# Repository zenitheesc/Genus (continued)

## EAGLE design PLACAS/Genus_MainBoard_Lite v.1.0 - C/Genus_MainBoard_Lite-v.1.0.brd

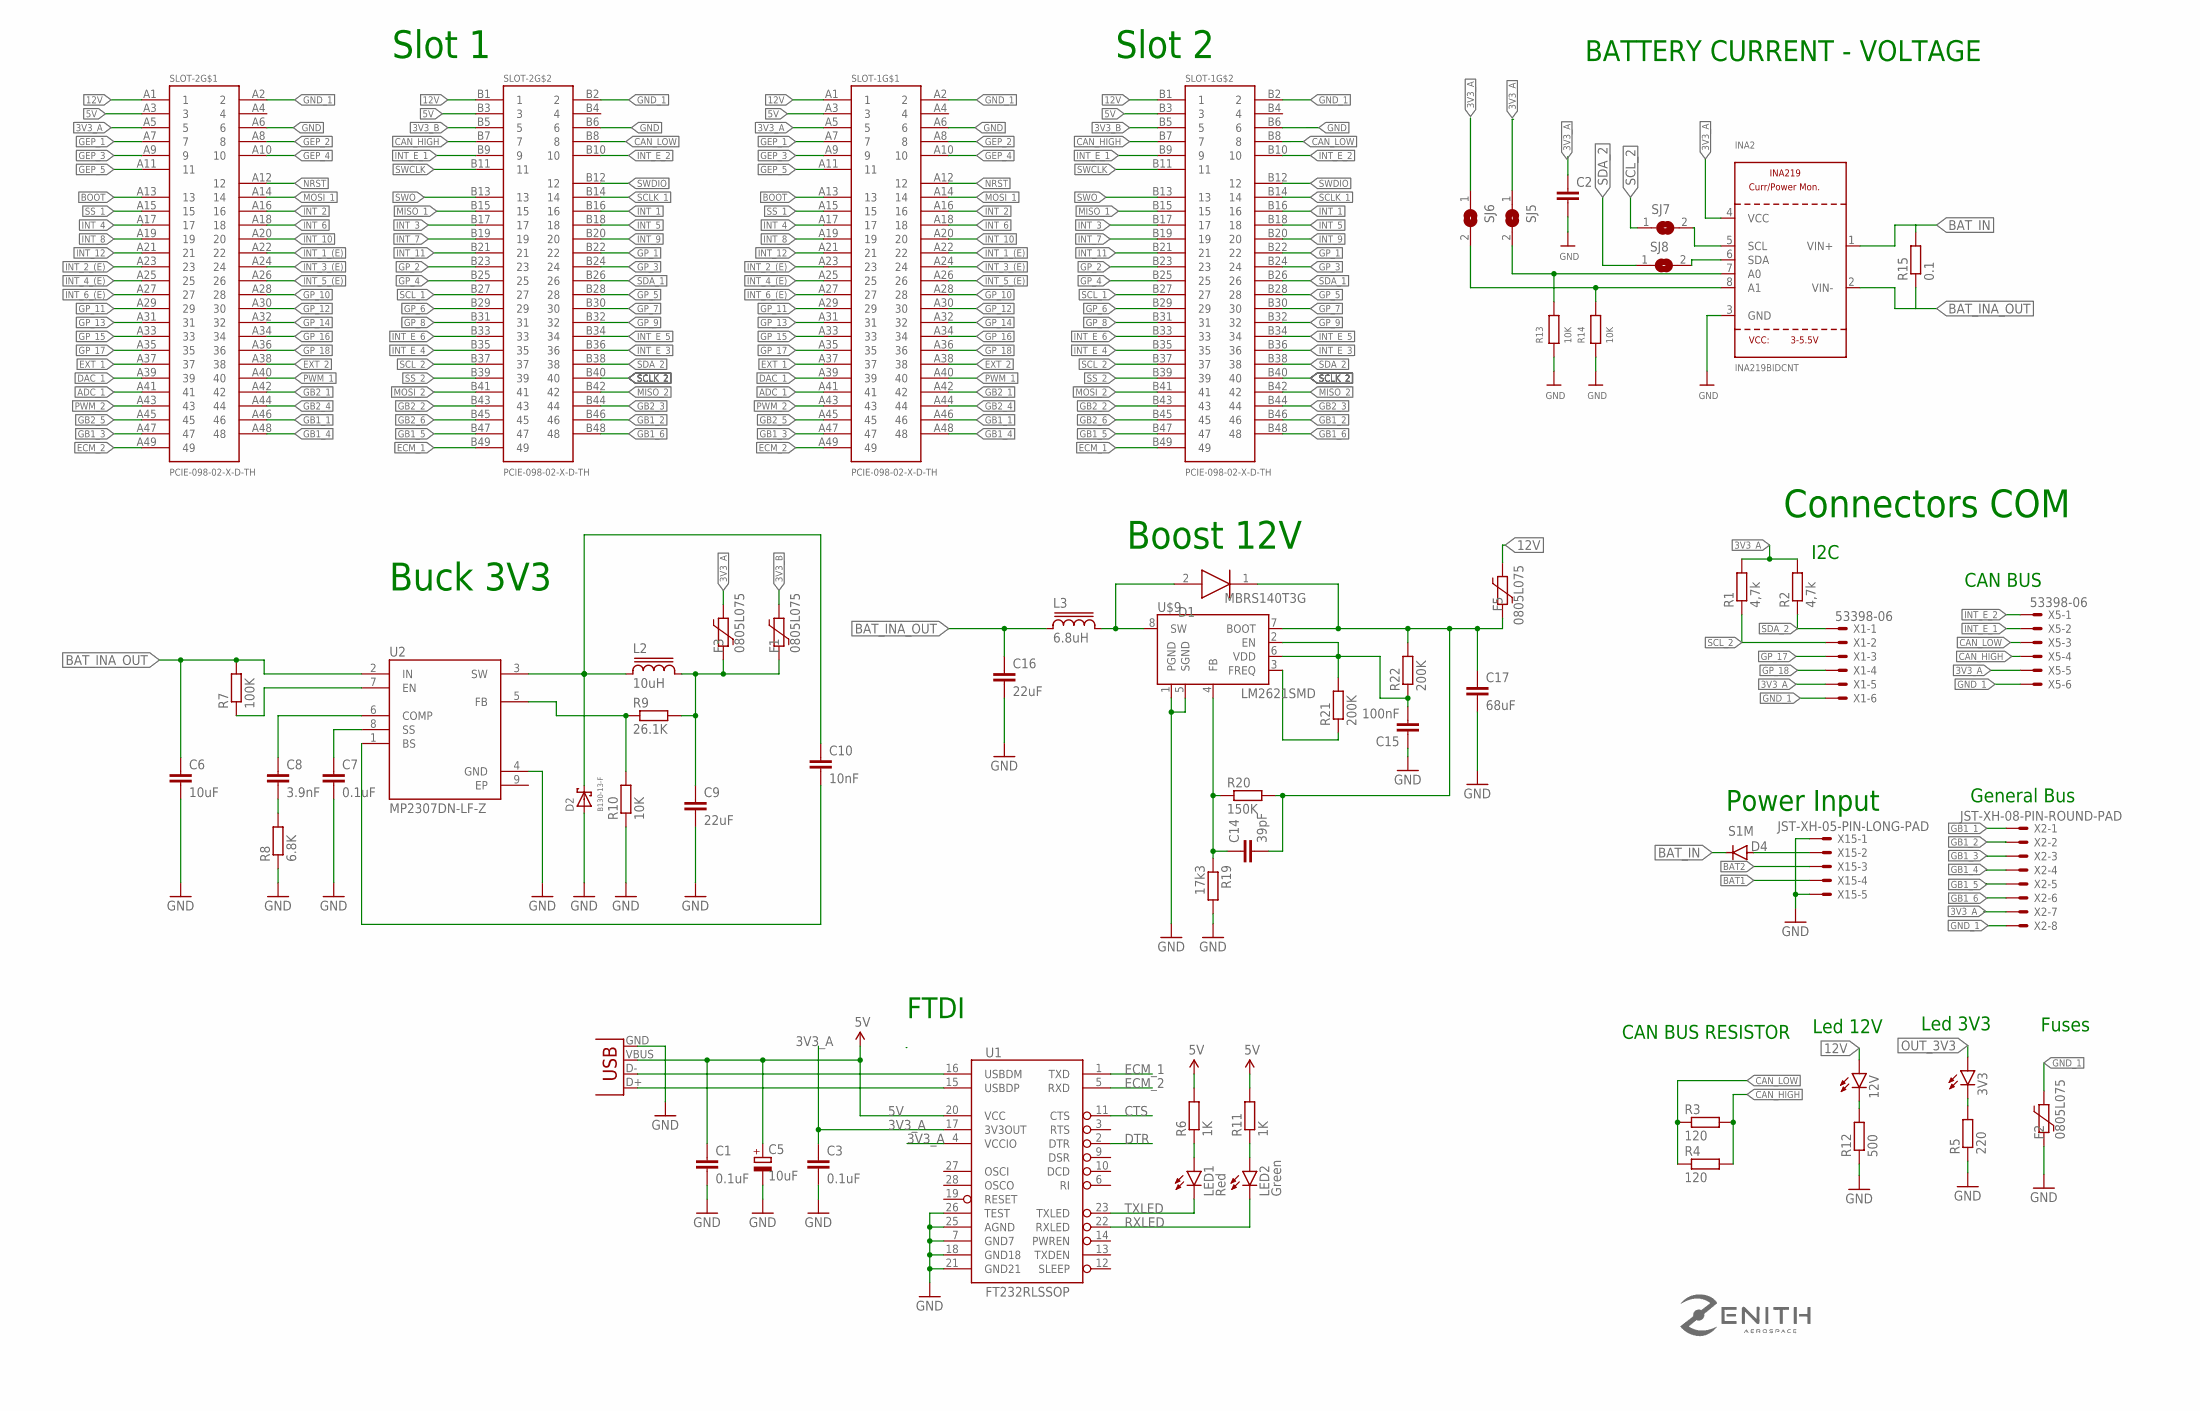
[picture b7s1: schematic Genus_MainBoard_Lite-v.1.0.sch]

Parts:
3V3, 12V: LEDCHIP-LED0805; CHIP-LED0805
C1, C3, C7: 0.1uF; C0805
C2: C-EUC0805; C0805
C5: 10uF; PANASONIC_B
C6: 10uF; C0805
C8: 3.9nF; C0805
C9: 22uF; C0805
C10: 10nF; C0805
C14: 39pF; C0805
C15: 100nF; C0805
C16: 22uF; C1210
C17: 68uF; C1210
D1: MBRS140T3G; DIOM5436X247N
D2: B130-13-F; SMA
D4: S1M; SMA
F1, F2, F3, F5: 0805L075; 0805L
INA2: INA219BIDCNT; SOT23-8
L2: 10uH; SRR1280
L3: 6.8uH; SRR1280
LED1: Red; CHIPLED_0805
LED2: Green; CHIPLED_0805
R1, R2: 4,7k; R0805
R3, R4: 120; R0805
R5: 220; R0805
R6, R11: 1K; R0805
R7: 100K; R0805
R8: 6.8K; R0805
R9: 26.1K; R0805
R10, R13, R14: 10K; R0805
R12: 500; R0805
R15: 0.1; R2512
R19: 17k3; R0805
R20: 150K; R0805
R21, R22: 200K; R0805
SJ5, SJ6, SJ7, SJ8: SOLDERJUMPERREFLOW_NOPASTE; SOLDERJUMPER_REFLOW_NOPASTE
SLOT-1, SLOT-2: PCIE-098-02-X-D-TH
U1: FT232RLSSOP; SSOP28DB
U2: MP2307DN-LF-Z; SOIC127P600X170-9N
U$9: LM2621SMD; MSOP-8
X1, X5: 53398-06
X2: JST-XH-08-PIN-ROUND-PAD; JST-XH-08-PACKAGE-ROUND-PAD
X3: USB-SMD-NS; USB-MINIB-NOSTOP
X15: JST-XH-05-PIN-LONG-PAD; JST-XH-05-PACKAGE-LONG-PAD

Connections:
3V3_A: C2.1, C3.1, F3.1, INA2.4 (VCC), R1.2, R2.2, SJ5.1, SJ6.1, SLOT-1.A5 (5), SLOT-2.A5 (5), U1.4 (VCCIO), U1.17 (3V3OUT), X1.5, X2.7, X5.5
3V3_B: F1.1, SLOT-1.B5 (5), SLOT-2.B5 (5)
5V: C1.1, C5.+, R6.2, R11.2, SLOT-1.A3 (3), SLOT-1.B3 (3), SLOT-2.A3 (3), SLOT-2.B3 (3), U1.20 (VCC), X3.VBUS
12V: 12V.A, F5.1, SLOT-1.A1 (1), SLOT-1.B1 (1), SLOT-2.A1 (1), SLOT-2.B1 (1)
ADC_1: SLOT-1.A41 (41), SLOT-2.A41 (41)
BAT1: X15.4
BAT2: X15.3
BAT_IN: D4.C, INA2.1 (VIN+), R15.2
BAT_INA_OUT: C6.1, C16.1, INA2.2 (VIN-), L3.1, R7.2, R15.1, U2.2 (IN)
BOOT: SLOT-1.A13 (13), SLOT-2.A13 (13)
CAN_HIGH: R3.2, R4.2, SLOT-1.B7 (7), SLOT-2.B7 (7), X5.4
CAN_LOW: R3.1, R4.1, SLOT-1.B8 (8), SLOT-2.B8 (8), X5.3
CTS: U1.11 (CTS)
DAC_1: SLOT-1.A39 (39), SLOT-2.A39 (39)
DTR: U1.2 (DTR)
ECM_1: SLOT-1.B49 (49), SLOT-2.B49 (49), U1.1 (TXD)
ECM_2: SLOT-1.A49 (49), SLOT-2.A49 (49), U1.5 (RXD)
EP: U2.9 (EP)
EXT_1: SLOT-1.A37 (37), SLOT-2.A37 (37)
EXT_2: SLOT-1.A38 (38), SLOT-2.A38 (38)
GB1_1: SLOT-1.A46 (46), SLOT-2.A46 (46), X2.1
GB1_2: SLOT-1.B46 (46), SLOT-2.B46 (46), X2.2
GB1_3: SLOT-1.A47 (47), SLOT-2.A47 (47), X2.3
GB1_4: SLOT-1.A48 (48), SLOT-2.A48 (48), X2.4
GB1_5: SLOT-1.B47 (47), SLOT-2.B47 (47), X2.5
GB1_6: SLOT-1.B48 (48), SLOT-2.B48 (48), X2.6
GB2_1: SLOT-1.A42 (42), SLOT-2.A42 (42)
GB2_2: SLOT-1.B43 (43), SLOT-2.B43 (43)
GB2_3: SLOT-1.B44 (44), SLOT-2.B44 (44)
GB2_4: SLOT-1.A44 (44), SLOT-2.A44 (44)
GB2_5: SLOT-1.A45 (45), SLOT-2.A45 (45)
GB2_6: SLOT-1.B45 (45), SLOT-2.B45 (45)
GEP_1: SLOT-1.A7 (7), SLOT-2.A7 (7)
GEP_2: SLOT-1.A8 (8), SLOT-2.A8 (8)
GEP_3: SLOT-1.A9 (9), SLOT-2.A9 (9)
GEP_4: SLOT-1.A10 (10), SLOT-2.A10 (10)
GEP_5: SLOT-1.A11 (11), SLOT-2.A11 (11)
GND: C1.2, C2.2, C3.2, C5.-, C6.2, C7.2, C9.2, C15.1, C16.2, C17.2, D2.A, F2.2, INA2.3 (GND), R5.1, R8.1, R10.1, R12.1, R13.1, R14.1, R19.2, SLOT-1.A6 (6), SLOT-1.B6 (6), SLOT-2.A6 (6), SLOT-2.B6 (6), U1.7 (GND7), U1.18 (GND18), U1.21 (GND21), U1.25 (AGND), U1.26 (TEST), U2.4 (GND), U$9.1 (PGND), U$9.5 (SGND), X3.GND, X15.1, X15.5
GND_1: F2.1, SLOT-1.A2 (2), SLOT-1.B2 (2), SLOT-2.A2 (2), SLOT-2.B2 (2), X1.6, X2.8, X5.6
GP_1: SLOT-1.B22 (22), SLOT-2.B22 (22)
GP_2: SLOT-1.B23 (23), SLOT-2.B23 (23)
GP_3: SLOT-1.B24 (24), SLOT-2.B24 (24)
GP_4: SLOT-1.B25 (25), SLOT-2.B25 (25)
GP_5: SLOT-1.B28 (28), SLOT-2.B28 (28)
GP_6: SLOT-1.B29 (29), SLOT-2.B29 (29)
GP_7: SLOT-1.B30 (30), SLOT-2.B30 (30)
GP_8: SLOT-1.B31 (31), SLOT-2.B31 (31)
GP_9: SLOT-1.B32 (32), SLOT-2.B32 (32)
GP_10: SLOT-1.A28 (28), SLOT-2.A28 (28)
GP_11: SLOT-1.A29 (29), SLOT-2.A29 (29)
GP_12: SLOT-1.A30 (30), SLOT-2.A30 (30)
GP_13: SLOT-1.A31 (31), SLOT-2.A31 (31)
GP_14: SLOT-1.A32 (32), SLOT-2.A32 (32)
GP_15: SLOT-1.A33 (33), SLOT-2.A33 (33)
GP_16: SLOT-1.A34 (34), SLOT-2.A34 (34)
GP_17: SLOT-1.A35 (35), SLOT-2.A35 (35), X1.3
GP_18: SLOT-1.A36 (36), SLOT-2.A36 (36), X1.4
INT_1: SLOT-1.B16 (16), SLOT-2.B16 (16)
INT_1_(E): SLOT-1.A22 (22), SLOT-2.A22 (22)
INT_2: SLOT-1.A16 (16), SLOT-2.A16 (16)
INT_2_(E): SLOT-1.A23 (23), SLOT-2.A23 (23)
INT_3: SLOT-1.B17 (17), SLOT-2.B17 (17)
INT_3_(E): SLOT-1.A24 (24), SLOT-2.A24 (24)
INT_4: SLOT-1.A17 (17), SLOT-2.A17 (17)
INT_4_(E): SLOT-1.A25 (25), SLOT-2.A25 (25)
INT_5: SLOT-1.B18 (18), SLOT-2.B18 (18)
INT_5_(E): SLOT-1.A26 (26), SLOT-2.A26 (26)
INT_6: SLOT-1.A18 (18), SLOT-2.A18 (18)
INT_6_(E): SLOT-1.A27 (27), SLOT-2.A27 (27)
INT_7: SLOT-1.B19 (19), SLOT-2.B19 (19)
INT_8: SLOT-1.A19 (19), SLOT-2.A19 (19)
INT_9: SLOT-1.B20 (20), SLOT-2.B20 (20)
INT_10: SLOT-1.A20 (20), SLOT-2.A20 (20)
INT_11: SLOT-1.B21 (21), SLOT-2.B21 (21)
INT_12: SLOT-1.A21 (21), SLOT-2.A21 (21)
INT_E_1: SLOT-1.B9 (9), SLOT-2.B9 (9), X5.2
INT_E_2: SLOT-1.B10 (10), SLOT-2.B10 (10), X5.1
INT_E_3: SLOT-1.B36 (36), SLOT-2.B36 (36)
INT_E_4: SLOT-1.B35 (35), SLOT-2.B35 (35)
INT_E_5: SLOT-1.B34 (34), SLOT-2.B34 (34)
INT_E_6: SLOT-1.B33 (33), SLOT-2.B33 (33)
MISO_1: SLOT-1.B15 (15), SLOT-2.B15 (15)
MISO_2: SLOT-1.B42 (42), SLOT-2.B42 (42)
MOSI_1: SLOT-1.A14 (14), SLOT-2.A14 (14)
MOSI_2: SLOT-1.B41 (41), SLOT-2.B41 (41)
unnamed: LED1.A, R6.1
unnamed: LED2.A, R11.1
unnamed: 12V.C, R12.2
unnamed: INA2.8 (A1), R14.2, SJ6.2
unnamed: D4.A, X15.2
unnamed: INA2.7 (A0), R13.2, SJ5.2
unnamed: R7.1, U2.7 (EN)
unnamed: C8.2, R8.2
unnamed: C7.1, U2.8 (SS)
unnamed: C8.1, U2.6 (COMP)
unnamed: C10.1, D2.C, L2.1, U2.3 (SW)
unnamed: R9.1, R10.2, U2.5 (FB)
unnamed: C10.2, U2.1 (BS)
unnamed: INA2.5 (SCL), SJ7.2
unnamed: INA2.6 (SDA), SJ8.2
unnamed: C14.1, R19.1, R20.1, U$9.4 (FB)
unnamed: D1.2 (A), L3.2, U$9.8 (SW)
unnamed: C15.2, R21.2, R22.1, U$9.2 (EN), U$9.6 (VDD)
unnamed: R21.1, U$9.3 (FREQ)
unnamed: 3V3.C, R5.2
NRST: SLOT-1.A12 (12), SLOT-2.A12 (12)
OUT: C14.2, C17.1, D1.1 (K), F5.2, R20.2, R22.2, U$9.7 (BOOT)
OUT_3V3: 3V3.A, C9.1, F1.2, F3.2, L2.2, R9.2
PWM_1: SLOT-1.A40 (40), SLOT-2.A40 (40)
PWM_2: SLOT-1.A43 (43), SLOT-2.A43 (43)
RXLED: LED2.C, U1.22 (RXLED)
SCLK_1: SLOT-1.B14 (14), SLOT-2.B14 (14)
SCLK_2: SLOT-1.B40 (40), SLOT-2.B40 (40)
SCL_1: SLOT-1.B27 (27), SLOT-2.B27 (27)
SCL_2: R1.1, SJ7.1, SLOT-1.B37 (37), SLOT-2.B37 (37), X1.2
SDA_1: SLOT-1.B26 (26), SLOT-2.B26 (26)
SDA_2: R2.1, SJ8.1, SLOT-1.B38 (38), SLOT-2.B38 (38), X1.1
SS_1: SLOT-1.A15 (15), SLOT-2.A15 (15)
SS_2: SLOT-1.B39 (39), SLOT-2.B39 (39)
SWCLK: SLOT-1.B11 (11), SLOT-2.B11 (11)
SWDIO: SLOT-1.B12 (12), SLOT-2.B12 (12)
SWO: SLOT-1.B13 (13), SLOT-2.B13 (13)
TXLED: LED1.C, U1.23 (TXLED)
USB_D+: U1.15 (USBDP), X3.D+
USB_D-: U1.16 (USBDM), X3.D-

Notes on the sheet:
Slot 1
Slot 2
CAN BUS
I2C
Power Input
Buck 3V3
Connectors COM
CAN BUS RESISTOR
Led 3V3
BATTERY CURRENT - VOLTAGE
Fuses
General Bus
FTDI
Boost 12V
Led 12V
C:/Users/marcu/Desktop/Ensino Superior/Graduação - Eng Elétrica/Zenith/zenith-v2.bmp

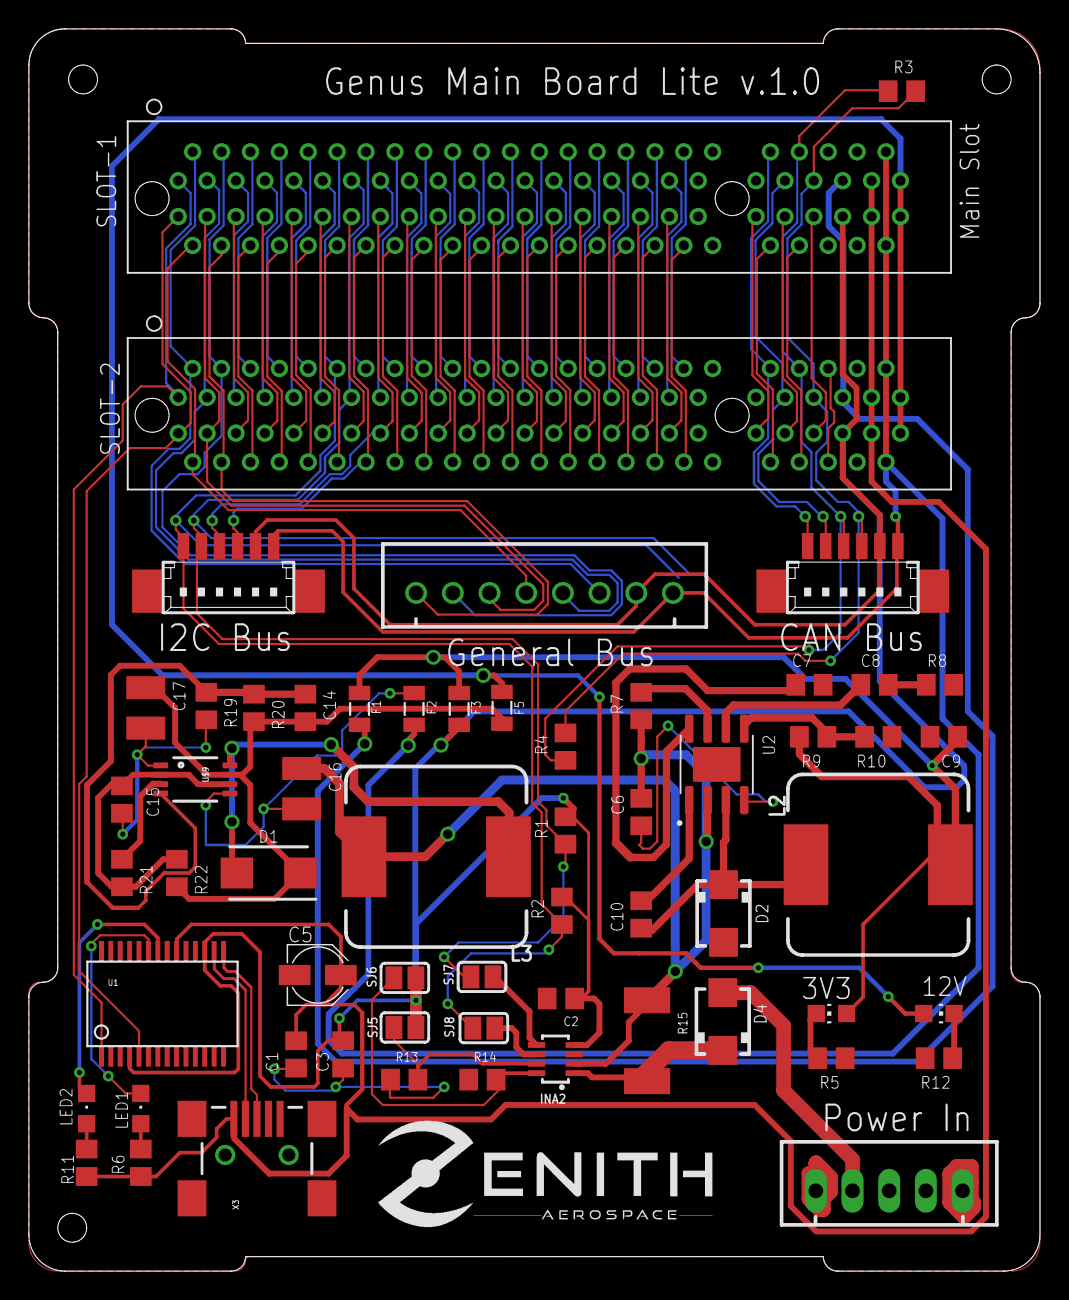
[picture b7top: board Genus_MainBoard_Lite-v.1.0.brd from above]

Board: 2 copper layers, 70.0 x 86.0 mm, 60 parts (0 on the bottom side), 120 nets.
